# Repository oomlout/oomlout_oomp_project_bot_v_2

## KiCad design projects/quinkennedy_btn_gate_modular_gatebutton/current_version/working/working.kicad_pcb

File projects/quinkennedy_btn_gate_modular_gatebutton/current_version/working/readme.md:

# btn_gate_modular
 
## summary 
* id: quinkennedy_btn_gate_modular_gatebutton
* user: quinkennedy
* name: btn_gate_modular
* board: gatebutton
* repo: https://github.com/quinkennedy/btn-gate-modular
* src_file_repo_kicad_pcb: GateButton.kicad_pcb
* src_file_repo_kicad_pcb_link: https://github.com/quinkennedy/btn-gate-modular/tree/main/GateButton.kicad_pcb

* src_file_repo_sch: GateButton.sch
* src_file_repo_sch_link: https://github.com/quinkennedy/btn-gate-modular/tree/main/GateButton.sch
* full details link: https://github.com/oomlout/oomlout_oomp_project_bot_v_2/tree/main/projects/quinkennedy_btn_gate_modular_gatebutton/current_version/working

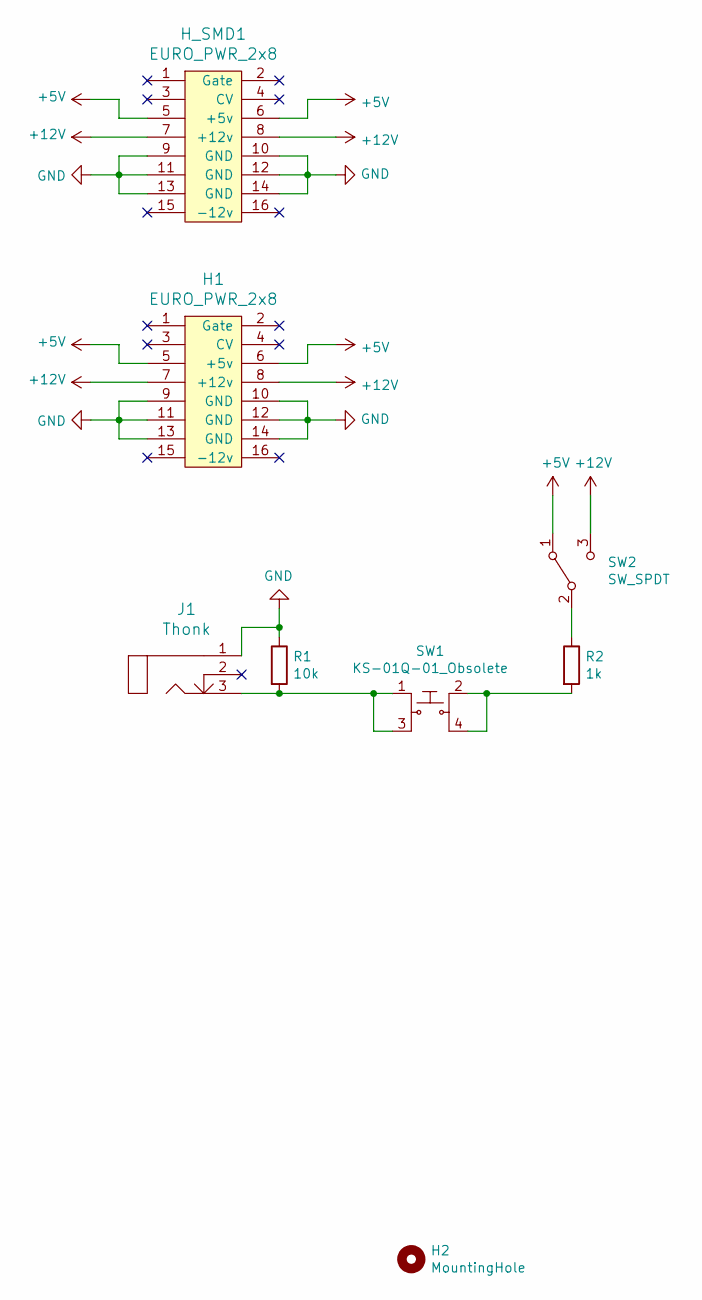
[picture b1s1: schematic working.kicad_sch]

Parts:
H1: EURO_PWR_2x8; PinHeader_2x08_P2.54mm_Vertical
H2: MountingHole; MountingHole_2.2mm_M2
H_SMD1: EURO_PWR_2x8; PinHeader_2x08_P2.54mm_Vertical_SMD
J1: Thonk; THONKICONN_mill
R1: 10k; Resistor_SMD+THTuniversal_0805to1206_RM10_HandSoldering
R2: 1k; Resistor_SMD+THTuniversal_0805to1206_RM10_HandSoldering
SW1: KS-01Q-01_Obsolete; PushButton_Round_D12mm_THT_KS-01Q-01; MPN KS-01Q-01; Digi-Key_PN EG4791-ND
SW2: SW_SPDT; Toggle_Switch_100SP1T1B4M2QE

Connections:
+5V: H1.5, H1.6 (+5v), H_SMD1.5, H_SMD1.6 (+5v), SW2.1 (A)
+12V: H1.7, H1.8 (+12v), H_SMD1.7, H_SMD1.8 (+12v), SW2.3 (C)
GND: H1.9, H1.10 (GND), H1.11, H1.12 (GND), H1.13, H1.14 (GND), H_SMD1.9, H_SMD1.10 (GND), H_SMD1.11, H_SMD1.12 (GND), H_SMD1.13, H_SMD1.14 (GND), J1.1, R1.1
unnamed: J1.3, R1.2, SW1.1, SW1.3
unnamed: R2.1, SW2.2 (B)
unnamed: R2.2, SW1.2, SW1.4

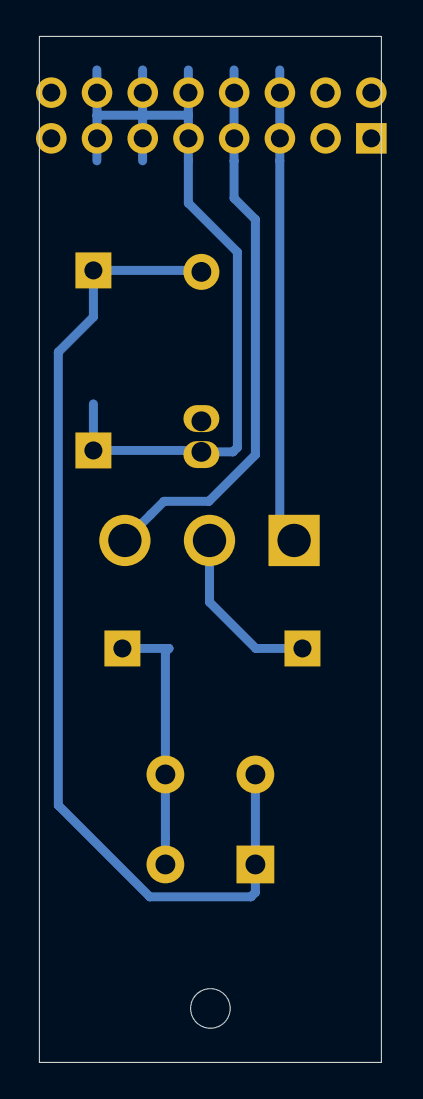
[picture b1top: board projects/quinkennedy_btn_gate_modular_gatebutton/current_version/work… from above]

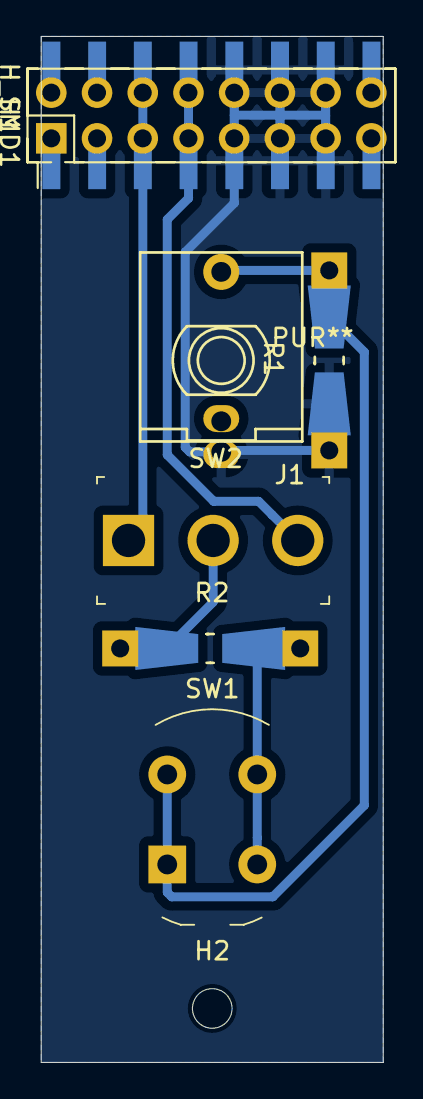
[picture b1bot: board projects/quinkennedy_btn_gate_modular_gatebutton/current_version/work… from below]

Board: 2 copper layers, 19.0 x 57.0 mm, 8 parts (8 on the bottom side), 6 nets.

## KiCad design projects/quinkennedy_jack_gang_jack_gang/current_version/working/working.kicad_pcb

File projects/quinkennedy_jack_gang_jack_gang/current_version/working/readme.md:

# jack_gang
 
## summary 
* id: quinkennedy_jack_gang_jack_gang
* user: quinkennedy
* name: jack_gang
* board: jack_gang
* repo: https://github.com/quinkennedy/jack-gang
* src_file_repo_kicad_pcb: jack-gang.kicad_pcb
* src_file_repo_kicad_pcb_link: https://github.com/quinkennedy/jack-gang/tree/main/jack-gang.kicad_pcb

* src_file_repo_sch: jack-gang.sch
* src_file_repo_sch_link: https://github.com/quinkennedy/jack-gang/tree/main/jack-gang.sch
* full details link: https://github.com/oomlout/oomlout_oomp_project_bot_v_2/tree/main/projects/quinkennedy_jack_gang_jack_gang/current_version/working

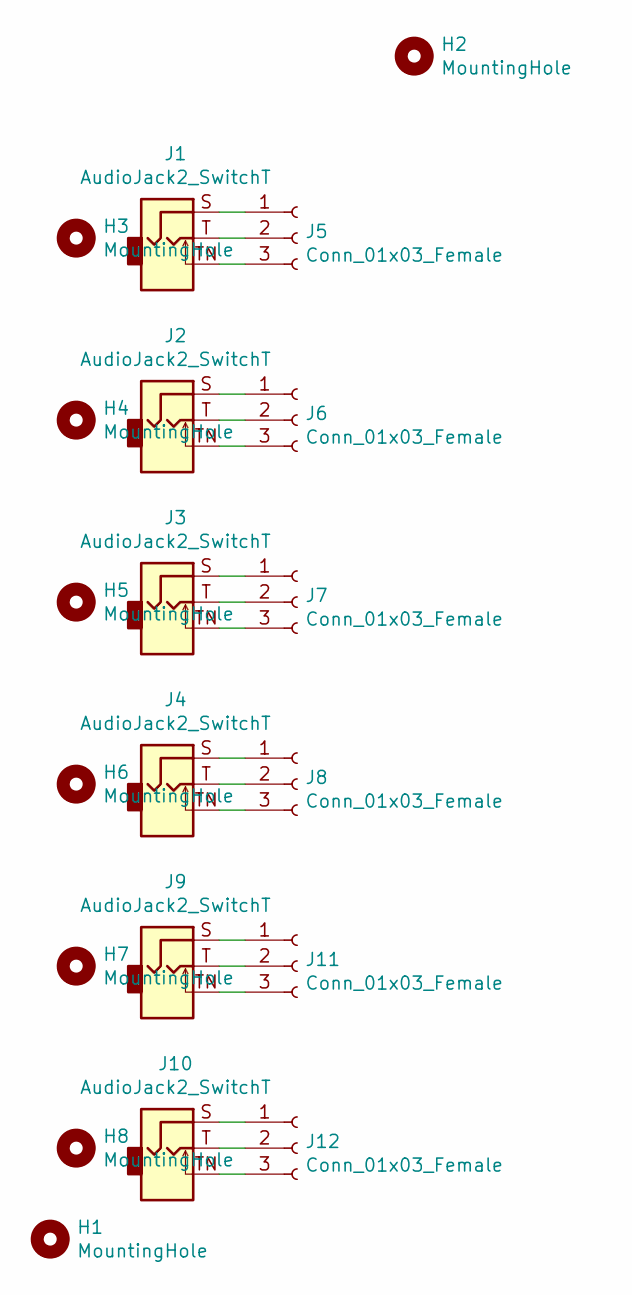
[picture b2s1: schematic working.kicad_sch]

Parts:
H1, H2: MountingHole; MountingHole_3.2mm_M3
H3, H4, H5, H6, H7, H8: MountingHole; jack_hole
J1, J2, J3, J4, J9, J10: AudioJack2_SwitchT; THONKICONN_mill_kicad
J5, J6, J7, J8, J11, J12: Conn_01x03_Female; PinHeader_1x03_P2.54mm_Vertical

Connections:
unnamed: J1.S, J5.1
unnamed: J1.T, J5.2
unnamed: J1.TN, J5.3
unnamed: J2.S, J6.1
unnamed: J2.T, J6.2
unnamed: J2.TN, J6.3
unnamed: J3.S, J7.1
unnamed: J3.T, J7.2
unnamed: J3.TN, J7.3
unnamed: J4.S, J8.1
unnamed: J4.T, J8.2
unnamed: J4.TN, J8.3
unnamed: J10.S, J12.1
unnamed: J10.T, J12.2
unnamed: J10.TN, J12.3
unnamed: J9.S, J11.1
unnamed: J9.T, J11.2
unnamed: J9.TN, J11.3

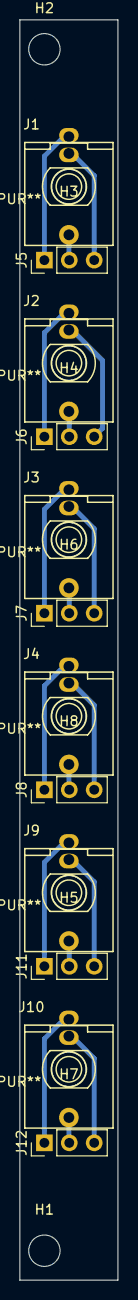
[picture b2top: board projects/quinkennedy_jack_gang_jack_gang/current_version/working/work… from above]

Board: 2 copper layers, 10.0 x 128.5 mm, 20 parts (0 on the bottom side), 18 nets.

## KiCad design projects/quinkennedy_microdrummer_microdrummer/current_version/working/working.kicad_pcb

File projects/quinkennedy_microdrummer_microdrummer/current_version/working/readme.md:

# microdrummer
 
## summary 
* id: quinkennedy_microdrummer_microdrummer
* user: quinkennedy
* name: microdrummer
* board: microdrummer
* repo: https://github.com/quinkennedy/microdrummer
* src_file_repo_kicad_pcb: hardware/board/microdrummer.kicad_pcb
* src_file_repo_kicad_pcb_link: https://github.com/quinkennedy/microdrummer/tree/master/hardware/board/microdrummer.kicad_pcb

* src_file_repo_sch: hardware/board/microdrummer.sch
* src_file_repo_sch_link: https://github.com/quinkennedy/microdrummer/tree/master/hardware/board/microdrummer.sch
* full details link: https://github.com/oomlout/oomlout_oomp_project_bot_v_2/tree/main/projects/quinkennedy_microdrummer_microdrummer/current_version/working

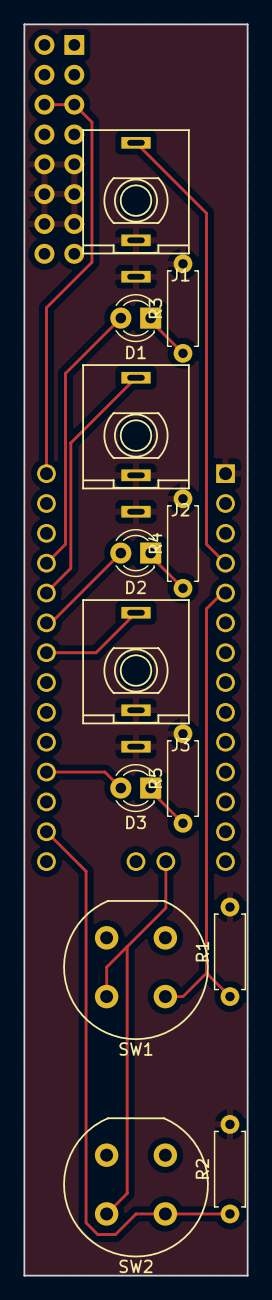
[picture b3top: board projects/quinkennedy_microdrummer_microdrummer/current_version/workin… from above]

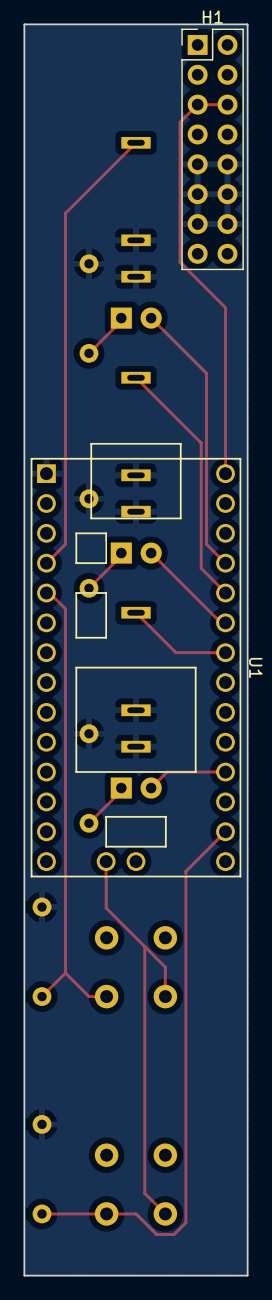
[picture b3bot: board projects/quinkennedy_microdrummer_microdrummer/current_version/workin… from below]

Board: 2 copper layers, 19.0 x 106.5 mm, 15 parts (2 on the bottom side), 14 nets.

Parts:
D1, D2, D3: LED; LED_D3.0mm_FlatTop
H1: EURO_PWR_2x8; Pin_Header_Straight_2x08_Pitch2.54mm
J1, J2, J3: Thonk; THONKICONN
R1, R2: 4.7k; R_Axial_DIN0207_L6.3mm_D2.5mm_P7.62mm_Horizontal
R3, R4, R5: 150; R_Axial_DIN0207_L6.3mm_D2.5mm_P7.62mm_Horizontal
SW1, SW2: SW_SPST; Push_E-Switch_KS01Q01
U1: Teensy3.2; Teensy30_31_32_LC_stdvgHeaders

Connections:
/BtnClr: R2.1, SW2.1, U1.21
/BtnIn: R1.1, SW1.1, U1.5
/GatLed: D2.2, U1.28
/GatOut: J2.3, U1.29
/SigIn: J1.3, U1.4
/SigLed: D1.2, U1.30
/TrgLed: D3.2, U1.23
/TrgOut: J3.3, U1.27
unnamed: D1.1, R3.1
unnamed: D2.1, R4.1
unnamed: D3.1, R5.1
unnamed: H1.5, H1.6, U1.33
unnamed: H1.9, H1.10, H1.11, H1.12, H1.13, H1.14, J1.1, J1.2, J2.1, J2.2, J3.1, J3.2, R1.2, R2.2, R3.2, R4.2, R5.2, U1.1
unnamed: SW1.2, SW2.2, U1.16

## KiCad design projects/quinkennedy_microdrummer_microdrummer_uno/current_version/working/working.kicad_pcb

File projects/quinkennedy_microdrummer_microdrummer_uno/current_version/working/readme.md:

# microdrummer
 
## summary 
* id: quinkennedy_microdrummer_microdrummer_uno
* user: quinkennedy
* name: microdrummer
* board: microdrummer_uno
* repo: https://github.com/quinkennedy/microdrummer
* src_file_repo_kicad_pcb: hardware/attiny85/microdrummer_uno.kicad_pcb
* src_file_repo_kicad_pcb_link: https://github.com/quinkennedy/microdrummer/tree/master/hardware/attiny85/microdrummer_uno.kicad_pcb

* src_file_repo_sch: hardware/attiny85/microdrummer_uno.sch
* src_file_repo_sch_link: https://github.com/quinkennedy/microdrummer/tree/master/hardware/attiny85/microdrummer_uno.sch
* full details link: https://github.com/oomlout/oomlout_oomp_project_bot_v_2/tree/main/projects/quinkennedy_microdrummer_microdrummer_uno/current_version/working

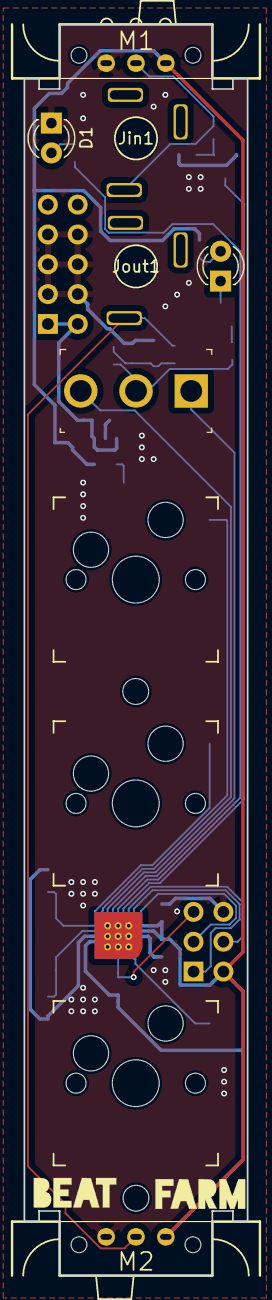
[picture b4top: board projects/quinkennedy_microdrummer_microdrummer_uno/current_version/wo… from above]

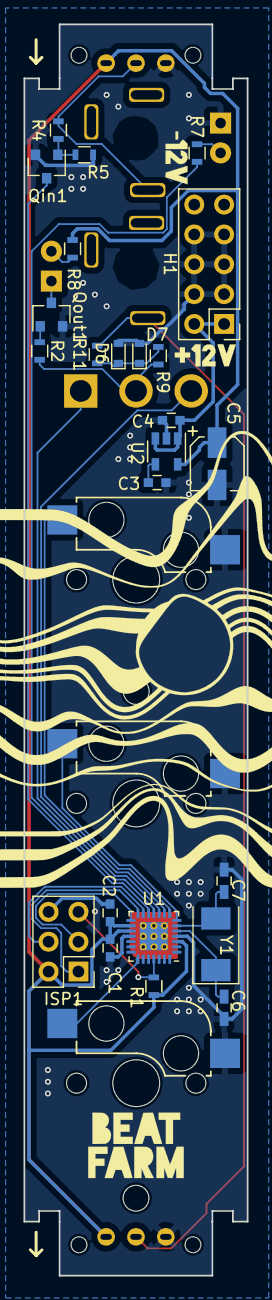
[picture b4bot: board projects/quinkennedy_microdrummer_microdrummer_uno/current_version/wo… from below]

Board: 2 copper layers, 19.0 x 106.5 mm, 34 parts (24 on the bottom side), 26 nets.

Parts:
C1: 10μF; C_0603
C2: 0.1μF; C_0603
C3: 470pF; C_0603
C4: 1μF; C_0603
C5: 2.2μF; CP_Elec_4x4.5
C6, C7: 30pF; C_0603_HandSoldering
D1: LED; LED_D3.0mm_FlatTop
D6: D_Zener; D_0603
D7: D_Schottky; D_0603
Dout1: LED; LED_D3.0mm_FlatTop
H1: EURO_PWR_2x5; PinHeader_2x05_P2.54mm_Vertical
ISP1: AVR-ISP-6; Pin_Header_Straight_2x03_Pitch2.54mm
Jin1: Thonk; schurter_3.5mm_mono_audio
Jout1: Thonk; schurter_3.5mm_mono_audio
M1: LITTLEBITS_MALE; LITTLE_BITS_MALE
M2: LITTLEBITS_FEMALE; LITTLE_BITS_FEMALE
Qin1: MMBT3904; SOT-23
Qout1: MMBT3904; SOT-23
R1: 10kΩ; R_0603
R2, R4: 100k; R_0603
R5: 1M; R_0603
R7, R8, R9, R11: 1k; R_0603
SELout1: SW_SPDT; Toggle_Switch_100SP1T1B4M2QE
U1: ATmega328-MMH; VQFN-28-1EP_4x4mm_P0.45mm_EP2.4x2.4mm_ThermalVias
U2: MIC5219-5.0YM5; SOT-23-5
Y1: 20MHz; Crystal_SMD_0603-2pin_6.0x3.5mm
bclr1: SW_SPST; Kailh_socket_MX
bin1: SW_SPST; Kailh_socket_MX_1.5v
brec1: SW_SPST; Kailh_socket_MX

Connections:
+5V: C1.2, C2.2, C5.1, ISP1.2, M1.V+, M2.V+, R1.1, R8.1, U1.3, U1.16, U1.17, U2.5
+12V: C4.1, H1.1, H1.2, U2.1, U2.3
/BTN_CLR: U1.8, bclr1.1
/BTN_IN: U1.22, bin1.1
/BTN_REC: U1.7, brec1.1
/IN_LED: R7.1, U1.11
/IN_SIGNAL: Qin1.3, U1.12
/ISP_MISO: ISP1.1, U1.14
/ISP_MOSI: ISP1.4, U1.13
/ISP_RST: ISP1.5, R1.2, U1.25
/ISP_SCK: ISP1.3, U1.15
/OUTPUT: M2.SIG, R11.1
/OUT_GATE: SELout1.1, U1.10
/OUT_TRIGGER: SELout1.3, U1.9
/RAW_OUTPUT: R2.1, R9.2, SELout1.2
/RAW_SIGNAL: M1.SIG, R4.2
GND: C1.1, C2.1, C3.2, C4.2, C5.2, C6.1, C7.1, D1.1, D6.2, D7.2, H1.3, H1.4, H1.5, H1.6, H1.7, H1.8, ISP1.6, M1.V-, M2.V-, Qin1.2, Qout1.2, R5.1, U1.4, U1.18, U1.29, U2.2, bclr1.2, bin1.2, brec1.2
unnamed: C3.1, U2.4
unnamed: C6.2, U1.5, Y1.1
unnamed: C7.2, U1.6, Y1.2
unnamed: D1.2, R7.2
unnamed: D6.1, D7.1, R9.1, R11.2
unnamed: Dout1.1, Qout1.3
unnamed: Dout1.2, R8.2
unnamed: Qin1.1, R4.1, R5.2
unnamed: Qout1.1, R2.2

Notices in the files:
projects/q61org_divergence_meter_dm_topboard/current_version/working/working.kicad_sch:
License: CC BY-SA 4.0 International
